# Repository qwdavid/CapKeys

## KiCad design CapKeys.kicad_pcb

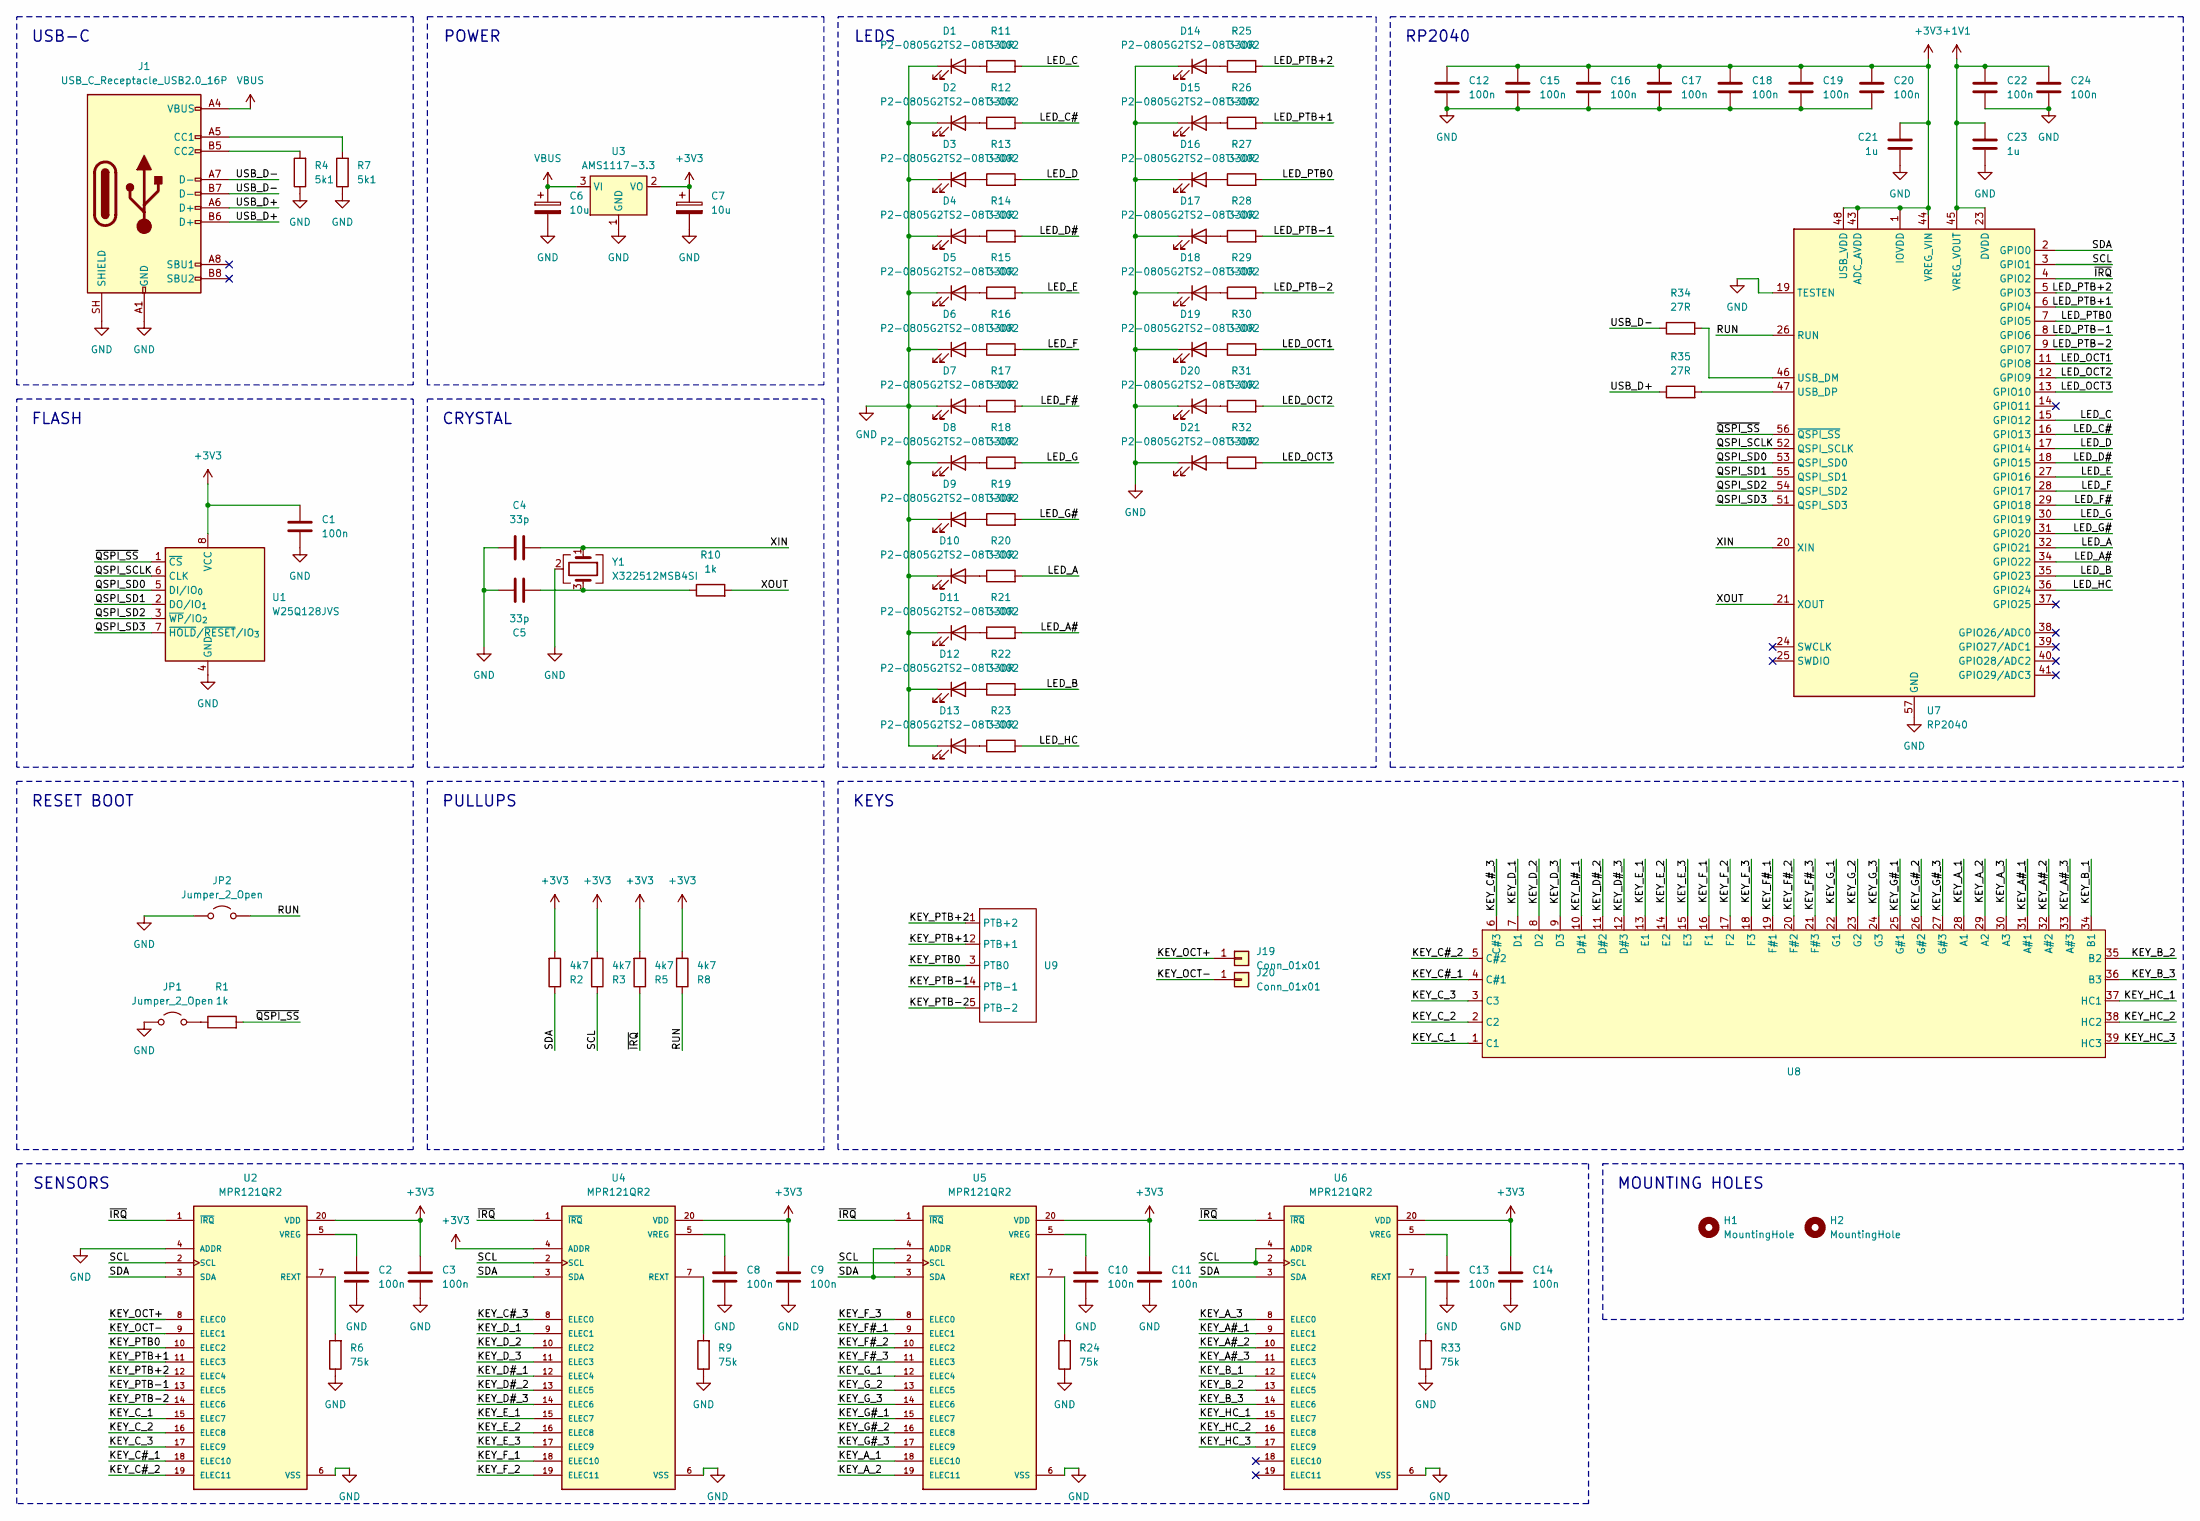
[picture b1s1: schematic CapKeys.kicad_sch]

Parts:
C1, C2, C3, C8, C9, C10, C11, C12, C13, C14, C15, C16, C17, C18, C19, C20, C22, C24: 100n; C_0402_1005Metric
C4, C5: 33p; C_0402_1005Metric
C6, C7: 10u; C_1206_3216Metric
C21, C23: 1u; C_0402_1005Metric
D1, D2, D3, D4, D5, D6, D7, D8, D9, D10, D11, D12, D13, D14, D15, D16, D17, D18, D19, D20, D21: P2-0805G2TS2-08T-002; D_0805_2012Metric
H1, H2: MountingHole; MountingHole_3.2mm_M3
J1: USB_C_Receptacle_USB2.0_16P; USB_C_Receptacle_HCTL_HC-TYPE-C-16P-01A
J19, J20: Conn_01x01; KEY_OTHER
JP1, JP2: Jumper_2_Open; SolderJumper-2_P1.3mm_Open_RoundedPad1.0x1.5mm
R1, R10: 1k; R_0402_1005Metric
R2, R3, R5, R8: 4k7; R_0402_1005Metric
R4, R7: 5k1; R_0402_1005Metric
R6, R9, R24, R33: 75k; R_0402_1005Metric
R11, R12, R13, R14, R15, R16, R17, R18, R19, R20, R21, R22, R23, R25, R26, R27, R28, R29, R30, R31, R32: 330R; R_0402_1005Metric
R34, R35: 27R; R_0402_1005Metric
U1: W25Q128JVS; SOIC-8_5.3x5.3mm_P1.27mm
U2, U4, U5, U6: MPR121QR2; UQFN-20_3x3mm_P0.4mm
U3: AMS1117-3.3; SOT-223-3_TabPin2
U7: RP2040; QFN-56-1EP_7x7mm_P0.4mm_EP3.2x3.2mm_ThermalVias
U8: KEYS
U9: PTB_KEYS
Y1: X322512MSB4SI; Crystal_SMD_3225-4Pin_3.2x2.5mm

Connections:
+1V1: C22.1, C23.1, C24.1, U7.23 (DVDD), U7.45 (VREG_VOUT), U7.50 (DVDD)
+3V3: C1.1, C3.1, C7.1, C9.1, C11.1, C12.1, C14.1, C15.1, C16.1, C17.1, C18.1, C19.1, C20.1, C21.1, R2.2, R3.2, R5.2, R8.2, U1.8 (VCC), U2.20 (VDD), U3.2 (VO), U4.4 (ADDR), U4.20 (VDD), U5.20 (VDD), U6.20 (VDD), U7.1 (IOVDD), U7.10 (IOVDD), U7.22 (IOVDD), U7.33 (IOVDD), U7.42 (IOVDD), U7.43 (ADC_AVDD), U7.44 (VREG_VIN), U7.48 (USB_VDD), U7.49 (IOVDD)
/KEY_A#_1: U6.9 (ELEC1), U8.31 (A#1)
/KEY_A#_2: U6.10 (ELEC2), U8.32 (A#2)
/KEY_A#_3: U6.11 (ELEC3), U8.33 (A#3)
/KEY_A_1: U5.18 (ELEC10), U8.28 (A1)
/KEY_A_2: U5.19 (ELEC11), U8.29 (A2)
/KEY_A_3: U6.8 (ELEC0), U8.30 (A3)
/KEY_B_1: U6.12 (ELEC4), U8.34 (B1)
/KEY_B_2: U6.13 (ELEC5), U8.35 (B2)
/KEY_B_3: U6.14 (ELEC6), U8.36 (B3)
/KEY_C#_1: U2.18 (ELEC10), U8.4 (C#1)
/KEY_C#_2: U2.19 (ELEC11), U8.5 (C#2)
/KEY_C#_3: U4.8 (ELEC0), U8.6 (C#3)
/KEY_C_1: U2.15 (ELEC7), U8.1 (C1)
/KEY_C_2: U2.16 (ELEC8), U8.2 (C2)
/KEY_C_3: U2.17 (ELEC9), U8.3 (C3)
/KEY_D#_1: U4.12 (ELEC4), U8.10 (D#1)
/KEY_D#_2: U4.13 (ELEC5), U8.11 (D#2)
/KEY_D#_3: U4.14 (ELEC6), U8.12 (D#3)
/KEY_D_1: U4.9 (ELEC1), U8.7 (D1)
/KEY_D_2: U4.10 (ELEC2), U8.8 (D2)
/KEY_D_3: U4.11 (ELEC3), U8.9 (D3)
/KEY_E_1: U4.15 (ELEC7), U8.13 (E1)
/KEY_E_2: U4.16 (ELEC8), U8.14 (E2)
/KEY_E_3: U4.17 (ELEC9), U8.15 (E3)
/KEY_F#_1: U5.9 (ELEC1), U8.19 (F#1)
/KEY_F#_2: U5.10 (ELEC2), U8.20 (F#2)
/KEY_F#_3: U5.11 (ELEC3), U8.21 (F#3)
/KEY_F_1: U4.18 (ELEC10), U8.16 (F1)
/KEY_F_2: U4.19 (ELEC11), U8.17 (F2)
/KEY_F_3: U5.8 (ELEC0), U8.18 (F3)
/KEY_G#_1: U5.15 (ELEC7), U8.25 (G#1)
/KEY_G#_2: U5.16 (ELEC8), U8.26 (G#2)
/KEY_G#_3: U5.17 (ELEC9), U8.27 (G#3)
/KEY_G_1: U5.12 (ELEC4), U8.22 (G1)
/KEY_G_2: U5.13 (ELEC5), U8.23 (G2)
/KEY_G_3: U5.14 (ELEC6), U8.24 (G3)
/KEY_HC_1: U6.15 (ELEC7), U8.37 (HC1)
/KEY_HC_2: U6.16 (ELEC8), U8.38 (HC2)
/KEY_HC_3: U6.17 (ELEC9), U8.39 (HC3)
/KEY_OCT+: J19.1 (Pin_1_1), U2.8 (ELEC0)
/KEY_OCT-: J20.1 (Pin_1_1), U2.9 (ELEC1)
/KEY_PTB0: U2.10 (ELEC2), U9.3 (PTB0)
/KEY_PTB+1: U2.11 (ELEC3), U9.2 (PTB+1)
/KEY_PTB+2: U2.12 (ELEC4), U9.1 (PTB+2)
/KEY_PTB-1: U2.13 (ELEC5), U9.4 (PTB-1)
/KEY_PTB-2: U2.14 (ELEC6), U9.5 (PTB-2)
/LED_A: R20.2, U7.32 (GPIO21)
/LED_A#: R21.2, U7.34 (GPIO22)
/LED_B: R22.2, U7.35 (GPIO23)
/LED_C: R11.2, U7.15 (GPIO12)
/LED_C#: R12.2, U7.16 (GPIO13)
/LED_D: R13.2, U7.17 (GPIO14)
/LED_D#: R14.2, U7.18 (GPIO15)
/LED_E: R15.2, U7.27 (GPIO16)
/LED_F: R16.2, U7.28 (GPIO17)
/LED_F#: R17.2, U7.29 (GPIO18)
/LED_G: R18.2, U7.30 (GPIO19)
/LED_G#: R19.2, U7.31 (GPIO20)
/LED_HC: R23.2, U7.36 (GPIO24)
/LED_OCT1: R30.2, U7.11 (GPIO8)
/LED_OCT2: R31.2, U7.12 (GPIO9)
/LED_OCT3: R32.2, U7.13 (GPIO10)
/LED_PTB0: R27.2, U7.7 (GPIO5)
/LED_PTB+1: R26.2, U7.6 (GPIO4)
/LED_PTB+2: R25.2, U7.5 (GPIO3)
/LED_PTB-1: R28.2, U7.8 (GPIO6)
/LED_PTB-2: R29.2, U7.9 (GPIO7)
/QSPI_SCLK: U1.6 (CLK), U7.52 (QSPI_SCLK)
/QSPI_SD0: U1.5 (DI/IO_{0}), U7.53 (QSPI_SD0)
/QSPI_SD1: U1.2 (DO/IO_{1}), U7.55 (QSPI_SD1)
/QSPI_SD2: U1.3 (~WP/IO_{2}), U7.54 (QSPI_SD2)
/QSPI_SD3: U1.7 (~HOLD/~RESET/IO_{3}), U7.51 (QSPI_SD3)
/RUN: JP2.2 (B), R8.1, U7.26 (RUN)
/SCL: R3.1, U2.2 (SCL), U4.2 (SCL), U5.2 (SCL), U6.2 (SCL), U6.4 (ADDR), U7.3 (GPIO1)
/SDA: R2.1, U2.3 (SDA), U4.3 (SDA), U5.3 (SDA), U5.4 (ADDR), U6.3 (SDA), U7.2 (GPIO0)
/USB_D+: J1.A6 (D+), J1.B6 (D+), R35.1
/USB_D-: J1.A7 (D-), J1.B7 (D-), R34.1
/XIN: C4.2, U7.20 (XIN), Y1.1
/XOUT: R10.2, U7.21 (XOUT)
/~IRQ: R5.1, U2.1 (~IRQ), U4.1 (~IRQ), U5.1 (~IRQ), U6.1 (~IRQ), U7.4 (GPIO2)
/~QSPI_SS: R1.2, U1.1 (~CS), U7.56 (~QSPI_SS)
GND: C1.2, C2.2, C3.2, C4.1, C5.1, C6.2, C7.2, C8.2, C9.2, C10.2, C11.2, C12.2, C13.2, C14.2, C15.2, C16.2, C17.2, C18.2, C19.2, C20.2, C21.2, C22.2, C23.2, C24.2, D1.1 (K), D2.1 (K), D3.1 (K), D4.1 (K), D5.1 (K), D6.1 (K), D7.1 (K), D8.1 (K), D9.1 (K), D10.1 (K), D11.1 (K), D12.1 (K), D13.1 (K), D14.1 (K), D15.1 (K), D16.1 (K), D17.1 (K), D18.1 (K), D19.1 (K), D20.1 (K), D21.1 (K), J1.A1 (GND), J1.A12 (GND), J1.B1 (GND), J1.B12 (GND), J1.SH (SHIELD), JP1.1 (A), JP2.1 (A), R4.1, R6.1, R7.1, R9.1, R24.1, R33.1, U1.4 (GND), U2.4 (ADDR), U2.6 (VSS), U3.1 (GND), U4.6 (VSS), U5.6 (VSS), U6.6 (VSS), U7.19 (TESTEN), U7.57 (GND), Y1.2 (G), Y1.4 (G)
unnamed: C5.2, R10.1, Y1.3
unnamed: D1.2 (A), R11.1
unnamed: D2.2 (A), R12.1
unnamed: D3.2 (A), R13.1
unnamed: D4.2 (A), R14.1
unnamed: D5.2 (A), R15.1
unnamed: D6.2 (A), R16.1
unnamed: D7.2 (A), R17.1
unnamed: D8.2 (A), R18.1
unnamed: D9.2 (A), R19.1
unnamed: D10.2 (A), R20.1
unnamed: D11.2 (A), R21.1
unnamed: D12.2 (A), R22.1
unnamed: D13.2 (A), R23.1
unnamed: D14.2 (A), R25.1
unnamed: D15.2 (A), R26.1
unnamed: D16.2 (A), R27.1
unnamed: D17.2 (A), R28.1
unnamed: D18.2 (A), R29.1
unnamed: D19.2 (A), R30.1
unnamed: D20.2 (A), R31.1
unnamed: D21.2 (A), R32.1
unnamed: J1.A5 (CC1), R7.2
unnamed: J1.B5 (CC2), R4.2
unnamed: JP1.2 (B), R1.1
unnamed: R6.2, U2.7 (REXT)
unnamed: C2.1, U2.5 (VREG)
unnamed: R9.2, U4.7 (REXT)
unnamed: C8.1, U4.5 (VREG)
unnamed: R24.2, U5.7 (REXT)
unnamed: C10.1, U5.5 (VREG)
unnamed: R33.2, U6.7 (REXT)
unnamed: C13.1, U6.5 (VREG)
unnamed: R34.2, U7.46 (USB_DM)
unnamed: R35.2, U7.47 (USB_DP)
VBUS: C6.1, J1.A4 (VBUS), J1.A9 (VBUS), J1.B4 (VBUS), J1.B9 (VBUS), U3.3 (VI)

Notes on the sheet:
PULLUPS
RP2040
CRYSTAL
KEYS
RESET BOOT
POWER
SENSORS
FLASH
USB-C
LEDS
MOUNTING HOLES

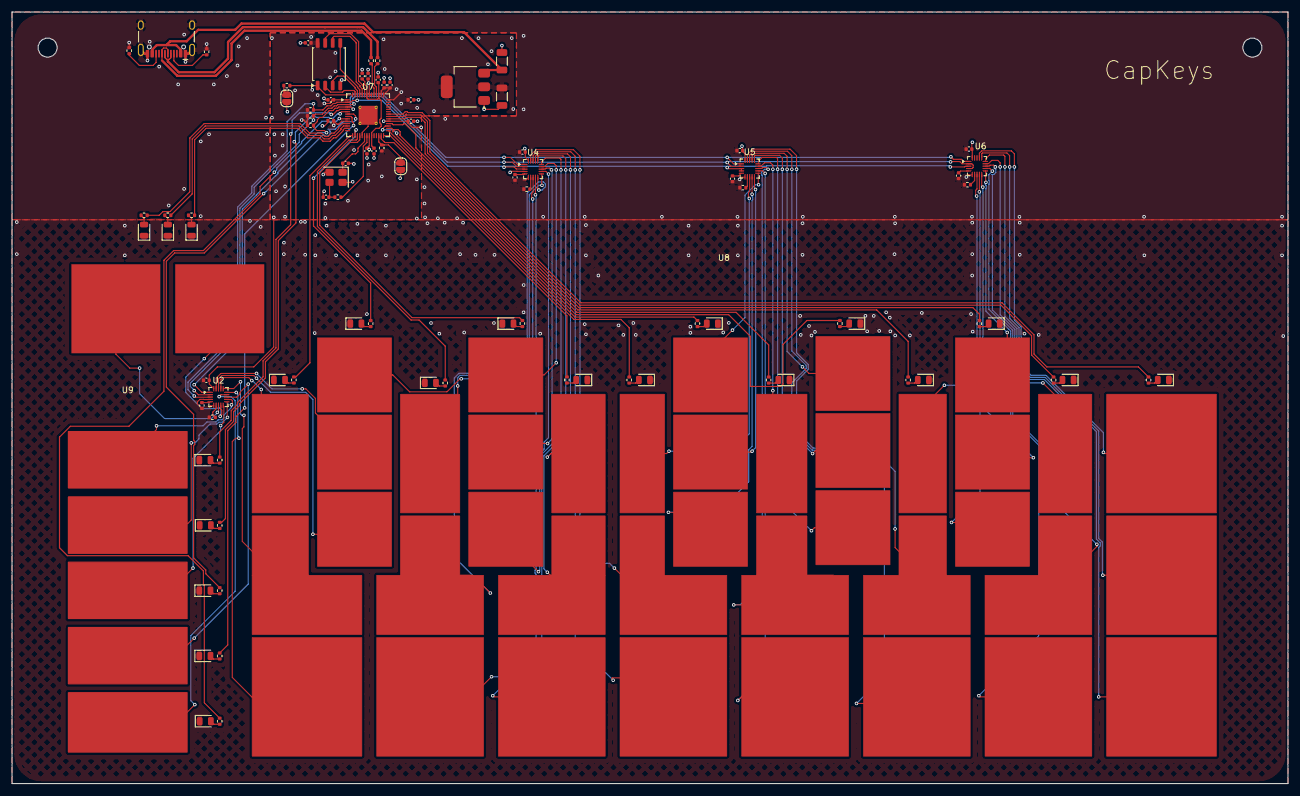
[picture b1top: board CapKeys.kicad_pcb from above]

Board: 4 copper layers, 215.0 x 130.0 mm, 97 parts (0 on the bottom side), 120 nets.
